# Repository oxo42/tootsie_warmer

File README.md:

# tootsie_warmer

Arudino controlled boot warmer using a Wemos D1 mini (ESP8266 variant) that can be controlled by Home Assitant over MQTT.

Pretend the LED is a relay that switches on the boot warmer

The circuit diagram for this is

## How does it work - Physical

* Pressing `SW_Add` (the lefthand button in the prototype) will add 15 minutes to a timer
* Pressing `SW_stop` will clear the timer and turn off the LED

## MQTT & Home Assistant

All communications happen over MQTT.

### Sensor Discovery

The device shows up in home assistant as a sensor in the active or idle states.

It has attributes of `duration` and `remaining` showing how long is left.  These fit really well with the [Lovelace Timer Bar Card](https://github.com/rianadon/timer-bar-card).  There is a weird thing with the timer bar card that it loses between 5 and 10 seconds due to how it works out time remaining.  I might fix this in https://github.com/oxo42/tootsie_warmer/issues/1

### Setting the timer remotely

Sending an integer to the MQTT topic `homeassistant/sensor/tootsie/set` will set the timer to that many seconds.  Once this is all hooked up, I intend HASS to send 3600s at 7am, just in time for me to leave at 8.

## But why?

I want to overengineer my boot warmer so that [Home Assistant](https://www.home-assistant.io/) can turn it on for me at 7am and I have warm ski boots at 8am. My intention is to pull the spring based timer out of a set of boot warmer and replace it with an arduino that controls a relay.

### Would it have been simpler to bypass the spring switch and use an off the shelf smart plug to control it?

You're not my friend any more, go away!

## Hardware gotchas

### Pin D8 cannot be held high at boot

At one point I had pin D8 connected to a pin on the LCD1602 that was high at boot and caused the boot to fail.

## References

* [ESP8266 Pinout Reference](https://randomnerdtutorials.com/esp8266-pinout-reference-gpios/)
* [Timer Bar Card](https://github.com/rianadon/timer-bar-card)

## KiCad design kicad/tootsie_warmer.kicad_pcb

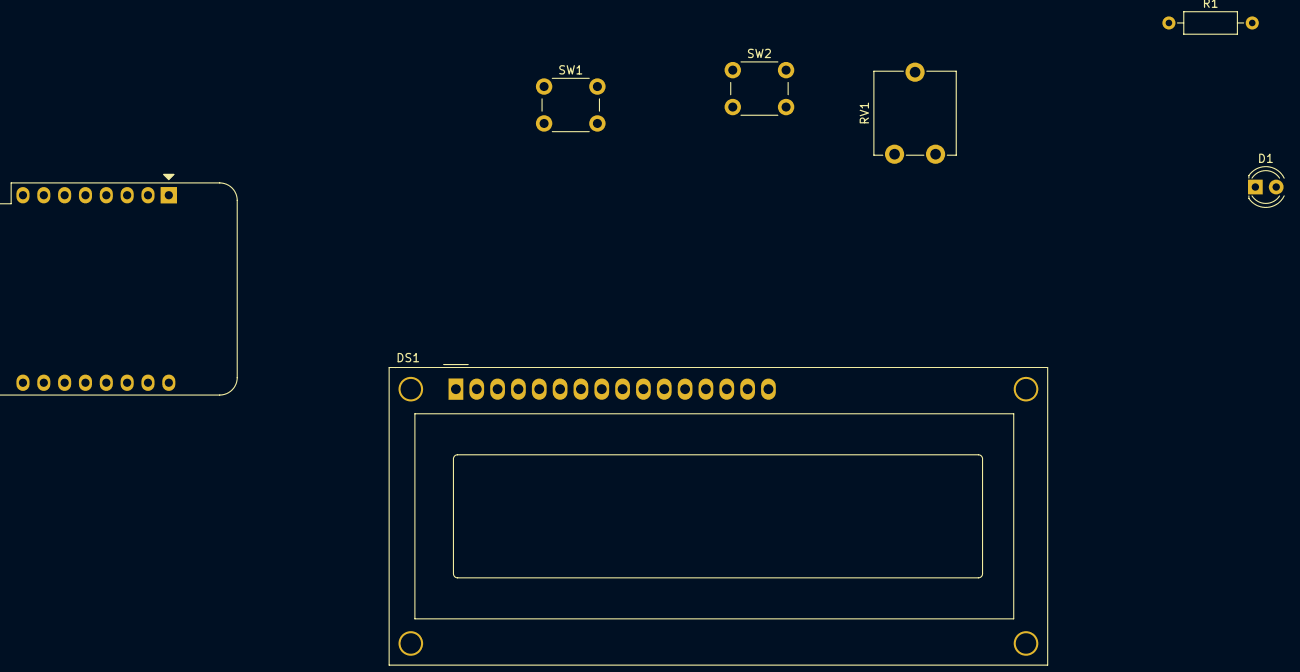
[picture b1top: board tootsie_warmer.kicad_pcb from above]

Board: 2 copper layers, 7 parts (0 on the bottom side), 13 nets, no tracks yet.

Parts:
D1: LED; LED_D4.0mm
DS1: WC1602A
R1: 220; R_Axial_DIN0207_L6.3mm_D2.5mm_P10.16mm_Horizontal
RV1: R_Potentiometer; Potentiometer_ACP_CA9-V10_Vertical
SW1: SW_Add; SW_PUSH_6mm_H4.3mm
SW2: SW_Stop; SW_PUSH_6mm_H4.3mm
U1: WeMos_D1_mini; WEMOS_D1_mini_light

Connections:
unnamed: D1.2 (A), R1.2
unnamed: DS1.3 (VO), RV1.2
unnamed: DS1.4 (RS), U1.14 (SCL/D1)
unnamed: DS1.6 (E), U1.7 (CS/D8)
unnamed: DS1.11 (D4), U1.3 (D0)
unnamed: DS1.12 (D5), U1.6 (MOSI/D7)
unnamed: DS1.13 (D6), U1.5 (MISO/D6)
unnamed: DS1.14 (D7), U1.4 (SCK/D5)
unnamed: R1.1, U1.11 (D4)
unnamed: SW1.2, U1.12 (D3)
unnamed: SW2.2, U1.13 (SDA/D2)
unnamed: DS1.2 (VDD), DS1.15 (LED(+)), RV1.3, U1.9 (5V)
unnamed: D1.1 (K), DS1.1 (VSS), DS1.5 (R/W), DS1.16 (LED(-)), RV1.1, SW1.1, SW2.1, U1.10 (GND)

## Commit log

2022-02-22 Initial import
2022-02-22 clean up
2022-02-22 Use HAMqttDevice
2022-02-22 Strip out old mqtt code
2022-02-22 Fix up timer stuff
2022-02-22 Bring device registry class into my project
2022-02-23 Add kicad files
2022-02-23 Updated timer attrs in readme
2022-02-23 Fix issue link
2022-02-26 Update state every 2 minutes to avoid going unavailable
2022-02-26 Update schema to have connector for relay
2022-02-26 Swap D2 & D4. Fixes #2
2022-03-01 Update kicad gitignore
2022-03-06 Using AsyncTimer 2.3.0
